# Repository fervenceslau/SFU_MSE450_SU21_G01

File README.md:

# MSE750_SU21_G01
Repository for the MSE450/750 course work

## Group Members
- Bilal Nurhusien
- Fernando Isensee
- Jason Epp

# Simulated Videogame Project
A simulated video game project based on Space Impact using the Tiva™ C Series board with a TM4C123GH6PM 32-bit Arm Cortex-M4F microcontroller and the Keil Embedded Development Tools for Arm.

## Corona
Based on the game Space Impact. Project files can be found in the Space Impact directory.

### Gameplay
The game I/O consists of 2 buttons and a joystick for x and y movement

-- Note: x movement unsupported in simulation

Use SW2 (PF0) for start/pause and SW1 (PF4) to fire lasers
use Ain1 (PE2) for y movement and Ain0 (PE3) for x movement

The goal of the game is to destroy the most enemies and last as long as possible.
The score is based on the number of enemies destroyed.
There are 3 lives at the beginning of the game, every time there is a collision with an enemy the ship will lose a life
when all lives are gone the game is over.

### Demo

### Development Success
* Successfully achieved all the goals of 1.0 release. Some bugs were caught, but many have been resolved
* After difficulties with the Labs, planning the git project allowed for much more seamless integration of each member's contributions. Only limited work was required to run the game after each member sections were complete

### Development Difficulties
* Some difficulties pertaining to the simulator. A lot of register access issues, and a lot of features that do not work in the simulator
* ADC is questionable when implementing in the simulator. Texas simulator allows you to select any ADC and it will work with the only adc channel implemented. Texas Simulator does not support more than 1 ADC from what I can tell
* Difficulties with project files and conflicts, Keil creates too many files when it builds so it's difficult to get rid of everything that isn't required. Due to the nature of Keil project files, it can make an unmanageable mess of the repository which are prone to conflicts and requiring numerous manual project file merges and make code reviews difficult
* Many minor bugs found when adding code together, though nothing catastrophic due to following previously planned structure

### Features
* SSI Control for Nokia 5110 Display - Ver 1.0 - Completed
* Game timing control using SysTick and counter - Ver 1.0 - Completed
* Screen update timer to control display updates - Ver 1.0 - Completed
* ADC for x and y control of joystick - Ver 1.0 - Completed
* Pushbutton control for start/pause and fire - Ver 1.0 - Completed
* Game engine for detecting state changes - Ver 1.0 - Completed
* Collision detection for sprites, and scorekeeping - Ver 1.0 - Completed
* UART to simulate/debug - Ver 1.0 - Unnecessary
* LED backlight control - Ver 2.0
* Buzzer implementation using PWM - Ver 2.0

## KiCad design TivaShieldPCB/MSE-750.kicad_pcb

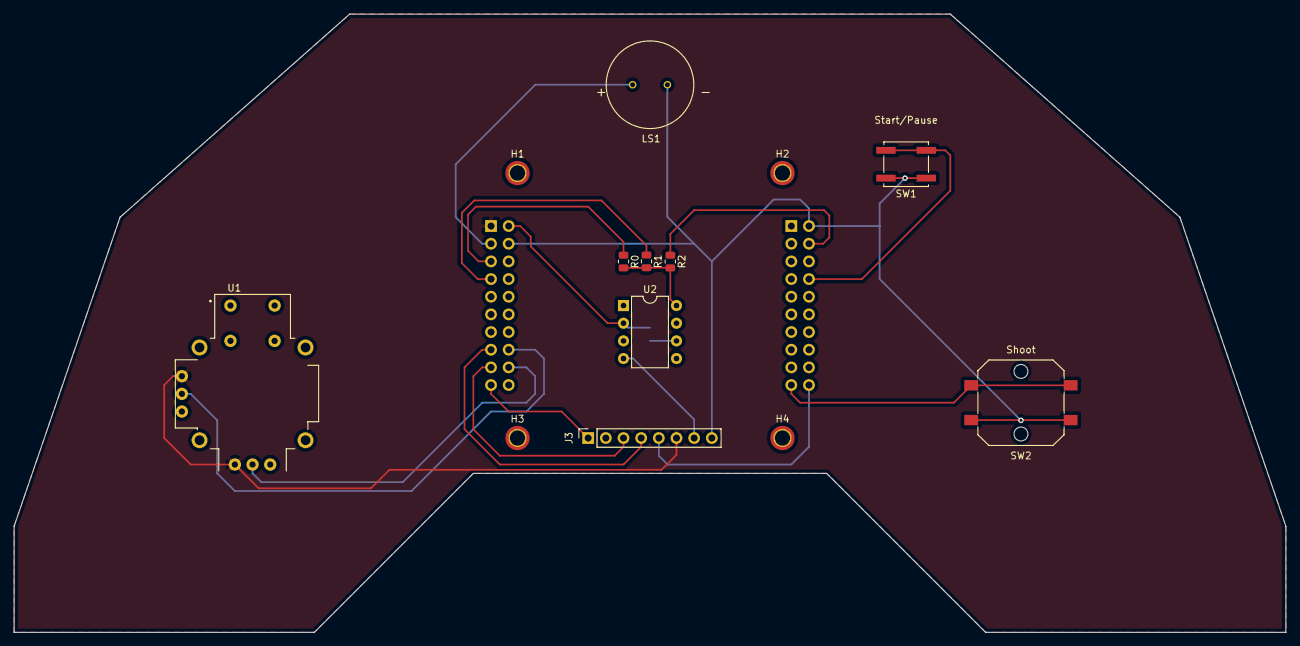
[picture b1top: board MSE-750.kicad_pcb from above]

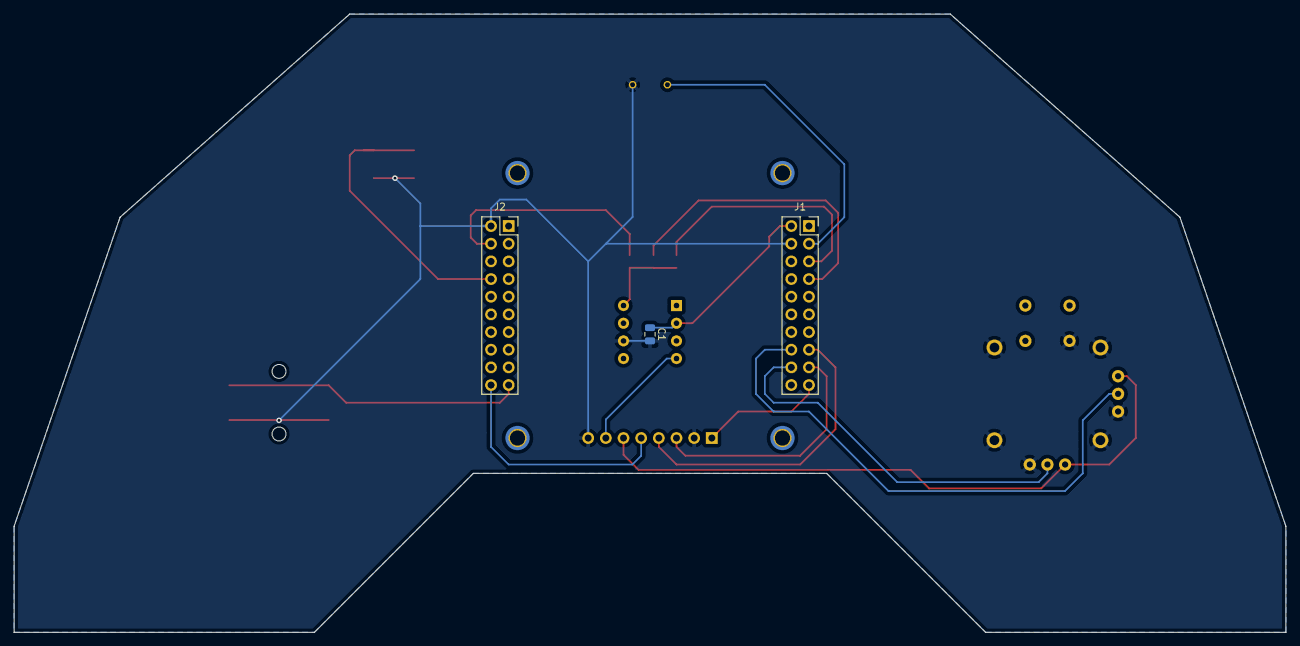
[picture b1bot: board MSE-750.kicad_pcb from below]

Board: 2 copper layers, 182.9 x 88.9 mm, 16 parts (3 on the bottom side), 17 nets.

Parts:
C1: 4.7uF; C_0805_2012Metric
H1, H2, H3, H4: MountingHole_Pad; MountingHole_2.2mm_M2_ISO7380_Pad_TopBottom
J1, J2: Conn_02x10_Top_Bottom; PinSocket_2x10_P2.54mm_VerticalPinLayout
J3: Conn_01x08; PinSocket_1x08_P2.54mm_Vertical
LS1: PKM13EPYH4002-B0; SPKR_PKM13EPYH4002-B0
R0: 1k65; R_0805_2012Metric
R1: 2k48; R_0805_2012Metric
R2: 4k93; R_0805_2012Metric
SW1: SW_Push; SW_Push_1P1T_NO_CK_KSC7xxJ
SW2: SW_Push; SW_Push_1P1T_NO_CK_PTS125Sx43PSMTR
U1: COM-09032; XDCR_COM-09032
U2: LM6321N; DIP-8_W7.62mm

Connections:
+3V3: J1.1, J3.6, U1.H1, U1.V1
BL: J3.7, U2.4
GNDREF: C1.2, J1.12, J2.11, J3.2, J3.8, LS1.N, SW1.2, SW2.2, U1.B2A, U1.H3, U1.S1, U1.S2, U1.S3, U1.S4, U1.V3, U2.6
unnamed: R0.2, R1.2, R2.2, U2.8
PA2: J2.20, J3.5
PA5: J1.8, J3.4
PA6: J1.9, J3.3
PA7: J1.10, J3.1
PB0: J1.3, R0.1
PB1: J1.4, R1.1
PB2: J2.12, R2.1
PB5: J1.2, LS1.P
PE2: J1.18, U1.V2
PE3: J1.19, U1.H2
PF0: J2.14, SW1.1
PF4: J2.10, SW2.1
VBUS: C1.1, J1.11, U2.2

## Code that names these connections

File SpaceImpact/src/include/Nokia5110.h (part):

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// Blue Nokia 5110
// ---------------
// Signal        (Nokia 5110) LaunchPad pin
// Reset         (RST, pin 1) connected to PA7
// SSI0Fss       (CE,  pin 2) connected to PA3
// Data/Command  (DC,  pin 3) connected to PA6
// SSI0Tx        (Din, pin 4) connected to PA5
// SSI0Clk       (Clk, pin 5) connected to PA2
// 3.3V          (Vcc, pin 6) power
// back light    (BL,  pin 7) not connected, consists of 4 white LEDs which draw ~80mA total
// Ground        (Gnd, pin 8) ground
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// 3.3V          (VCC, pin 1) power
// Ground        (GND, pin 2) ground
// SSI0Fss       (SCE, pin 3) connected to PA3
// Reset         (RST, pin 4) connected to PA7
// Data/Command  (D/C, pin 5) connected to PA6
// SSI0Tx        (DN,  pin 6) connected to PA5
// SSI0Clk       (SCLK, pin 7) connected to PA2
// back light    (LED, pin 8) not connected, consists of 4 white LEDs which draw ~80mA total

// Maximum dimensions of the LCD, although the pixels are
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

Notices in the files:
SpaceImpact/src/include/Nokia5110.h:
"Embedded Systems: Introduction to ARM Cortex M Microcontrollers",
ISBN: 978-1469998749, Jonathan Valvano, copyright (c) 2014
Copyright 2014 by Jonathan W. Valvano, valvano@mail.utexas.edu
